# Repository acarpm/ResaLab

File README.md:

# ResaLab

---

**ResaLab** est un projet multidomaine ayant pour objectif de **simplifier et centraliser la procédure de réservation des ressources du FabLab**.  
Il vise à offrir une plateforme fiable, intuitive et interconnectée entre le site web, la base de données et les équipements physiques du FabLab.

---

# 📌 Module matériel – Interface HMI

Le module ResaLab est une **interface homme-machine (IHM)** destinée à être installée directement sur les équipements du FabLab :

- Imprimantes 3D  
- Brodeuses numériques  
- Découpeuses laser  

## 🧩 Composition du module

- 🖥️ Écran **e-ink 2.9"**
- 🔴🟠🟢 Trois LED haute puissance (3W)
- 🔘 Trois boutons lumineux
- 🧠 Module **ESP32-C3**
- ⚡ Alimentation USB-C
- 📐 PCB sur mesure (PCB-A)

---

# 🎯 Fonctionnalités principales

Le module permet :

- ✅ D’afficher l’état de la machine (Disponible / Réservée / En cours)
- 📅 De synchroniser les réservations avec le serveur
- 🔐 De valider localement la présence de l’utilisateur
- 💡 De fournir un retour visuel clair via LED haute puissance
- 🌐 De communiquer en Wi-Fi avec la plateforme centrale

---

# ⚙️ Configuration requise

Certaines constantes doivent être définies dans le firmware :

```cpp
const char* deviceId = "00000001";  // ID du device enregistré sur le serveur

Un fichier identifier.h doit être créé et contenir :

const char* ssid = "";
const char* password = "";
const String serverUrl = "";

``` 

Ce fichier doit être inclus dans le code principal.

---

## Architecture générale du projet

Le projet est divisé en plusieurs domaines complémentaires :

**Site Web**
Plateforme de réservation en ligne
Gestion des utilisateurs et des droits d'accès
Gestion des réservations (création, modification, consultation)
Base de données centralisée
Historique d’utilisation

**Gestion des transactions / crédits**
Carte électronique (ESP32-C3)
Interface Homme-Machine locale
Validation des réservations via API serveur
Autorisation d’accès à l’équipement

Affichage des informations sur écran e-ink
Pilotage des LED 3W
Communication Wi-Fi sécurisée

**Modélisation du boîtier**
Conception 3D du boîtier
Intégration ergonomique des boutons et LEDs
Adaptation aux contraintes d’impression 3D
Optimisation pour maintenance et production FabLab

Voici certaines contraintes à tenir en compte:
Alimentation
Entrée : 5V
Conversion vers 3.3V / 3A
Capacité 3A dimensionnée pour :

Pics Wi-Fi
LED haute puissance
Écran e-ink

## Gestion des LED 3W
Pads TP3 à TP8
Pilotage via transistors Q1, Q2, Q3
Couleurs :
🔴 Rouge
🟠 Orange
🟢 Vert

*GPIO LED*
green  = 0
orange = 9
red    = 1

*Boutons lumineux*
Pads TP9 à TP17

## Interface écran e-ink (SPI 4 lignes)

Écran 2.9 connecté via SPI. https://github.com/WeActStudio/WeActStudio.EpaperModule

Mapping GPIO
MOSI : 7
SCLK : 6
CS   : 10
DC   : 8
RST  : 3
BUSY : 2

Connexion prévue via dupont wires.

GPIO supplémentaires

Les GPIO restants sont exposés via le connecteur J3.
Permet d’ajouter des périphériques ou de réaliser des tests.

## État du projet

Version actuelle : PCB-A (Proof of Concept)

## État du projet

La première version de la PCB a servi de **Proof of Concept (PoC)**.

Une nouvelle révision est prévue afin de :

- Corriger les défauts de la V1
- Permettre la programmation directement via le port **USB-C d’alimentation**
- Simplifier l’intégration et améliorer la fiabilité

---

## Roadmap (prévisionnelle)

- [ ] Révision PCB V2
- [ ] Intégration module ESP32-C3
- [ ] Support complet OTA
- [ ] Intégration avec le système de réservation (backend ResaLab)

---

## Statut

Projet en développement actif.  
Version actuelle : Prototype fonctionnel (PoC).

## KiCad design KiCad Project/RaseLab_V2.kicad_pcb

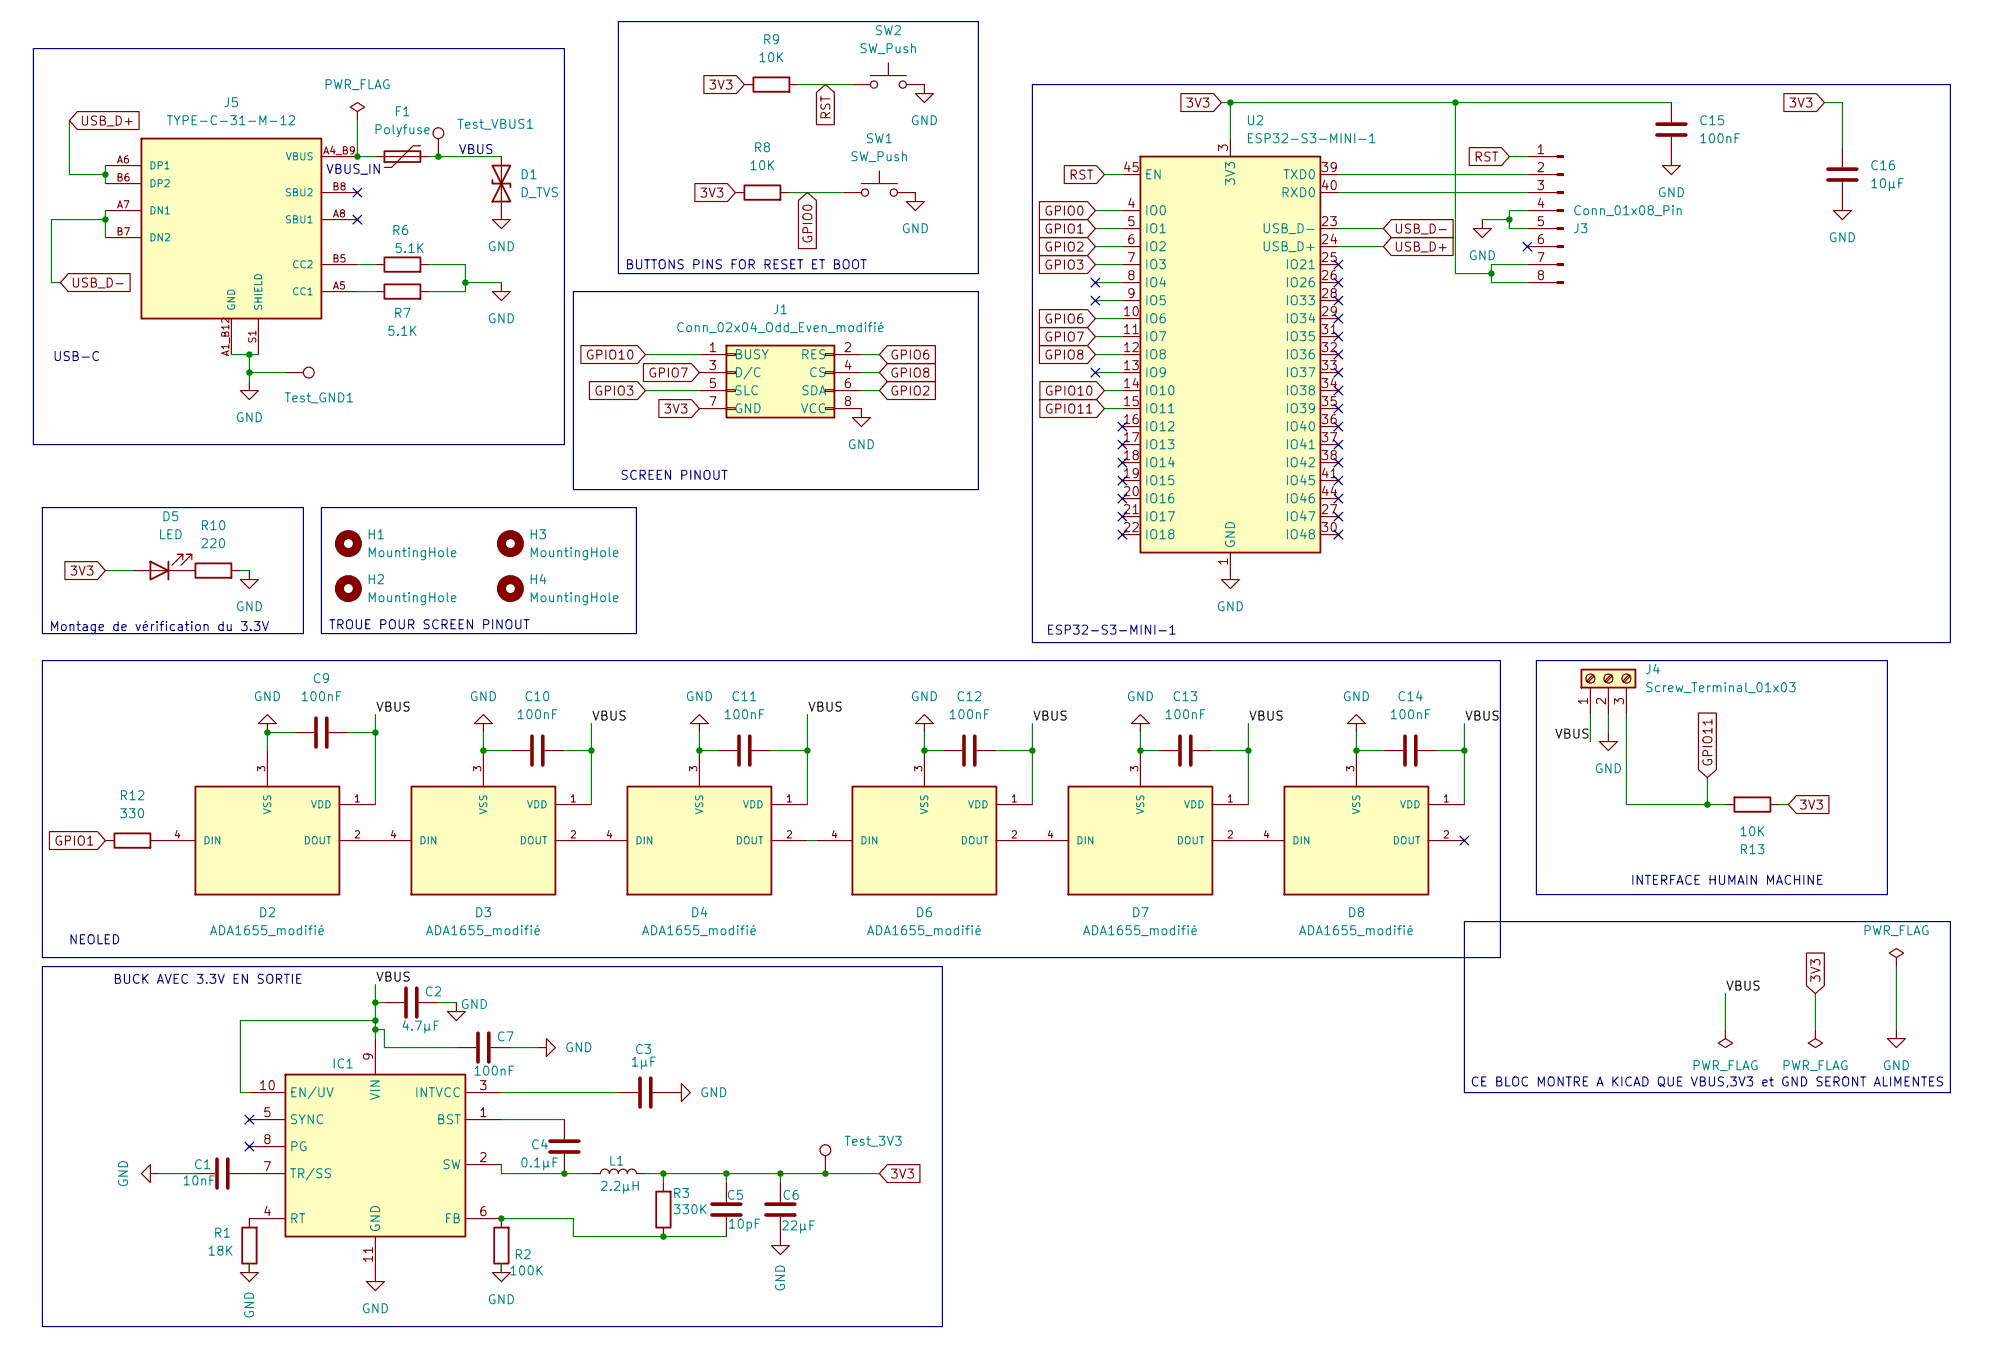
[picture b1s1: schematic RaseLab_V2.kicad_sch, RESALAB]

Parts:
C1: 10nF; C_0603_1608Metric
C2: 4.7µF; C_0603_1608Metric
C3: 1µF; C_0603_1608Metric
C4: 0.1µF; C_0603_1608Metric
C5: 10pF; C_0603_1608Metric
C6: 22µF; C_0603_1608Metric
C7, C9, C10, C11, C12, C13, C14, C15: 100nF; C_0603_1608Metric
C16: 10µF; C_0603_1608Metric
D1: D_TVS; D_SOD-123
D2, D3, D4, D6, D7, D8: ADA1655_modifié; LED_WS2812B_PLCC4_5.0x5.0mm_P3.2mm; PARTREV N/A
D5: LED; LED_0603_1608Metric
F1: Polyfuse; Fuse_1206_3216Metric
H1, H2, H3, H4: MountingHole; MountingHole_2.2mm_M2
IC1: LT8607EMSE#TRPBF; SOP50P490X110-11N; Mouser Part Number 584-LT8607EMSE#TRPBF
J1: Conn_02x04_Odd_Even_modifié; PinHeader_2x04_P2.54mm_Vertical
J3: Conn_01x08_Pin; PinHeader_1x08_P2.54mm_Horizontal
J4: Screw_Terminal_01x03; TerminalBlock_MaiXu_MX126-5.0-03P_1x03_P5.00mm
J5: TYPE-C-31-M-12; HRO_TYPE-C-31-M-12; PARTREV 2020.12.08
L1: 2.2µH; L_2010_5025Metric
R1: 18K; R_0603_1608Metric
R2: 100K; R_0603_1608Metric
R3: 330K; R_0603_1608Metric
R6, R7: 5.1K; R_0603_1608Metric
R8, R9, R13: 10K; R_0603_1608Metric
R10: 220; R_0603_1608Metric
R12: 330; R_0603_1608Metric
SW1, SW2: SW_Push; SW_SPST_PTS645Sx43SMTR92
Test_3V3: TestPoint; TestPoint_Pad_1.0x1.0mm
Test_GND1: TestPoint; TestPoint_Pad_1.0x1.0mm
Test_VBUS1: TestPoint; TestPoint_Pad_1.0x1.0mm
U2: ESP32-S3-MINI-1; XCVR_ESP32-S3-MINI-1-N8

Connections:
3V3: C5.2, C6.2, C15.1, C16.1, D5.2 (A), J1.7 (GND), J3.7, J3.8, L1.2, R3.2, R8.1, R9.1, R13.1, Test_3V3.1 (1_1), U2.3 (3V3)
GND: C1.2, C2.1, C3.1, C6.1, C7.1, C9.1, C10.1, C11.1, C12.1, C13.1, C14.1, C15.2, C16.2, D1.1 (A1), D2.3 (VSS), D3.3 (VSS), D4.3 (VSS), D6.3 (VSS), D7.3 (VSS), D8.3 (VSS), IC1.11 (GND), J1.8 (VCC), J3.4, J3.5, J4.2, J5.A1_B12 (GND), J5.S1 (SHIELD), R1.1, R2.1, R6.2, R7.2, R10.2, SW1.2, SW2.2, Test_GND1.1 (1_1), U2.1 (GND), U2.2 (GND), U2.42 (GND), U2.43 (GND), U2.46 (GND), U2.47 (GND), U2.48 (GND), U2.49 (GND), U2.50 (GND), U2.51 (GND), U2.52 (GND), U2.53 (GND), U2.54 (GND), U2.55 (GND), U2.56 (GND), U2.57 (GND), U2.58 (GND), U2.59 (GND), U2.60 (GND), U2.61 (GND), U2.62 (GND), U2.63 (GND), U2.64 (GND), U2.65 (GND)
GPIO0: R8.2, SW1.1, U2.4 (IO0)
GPIO1: R12.1, U2.5 (IO1)
GPIO2: J1.6 (SDA), U2.6 (IO2)
GPIO3: J1.5 (SLC), U2.7 (IO3)
GPIO6: J1.2 (RES), U2.10 (IO6)
GPIO7: J1.3 (D/C), U2.11 (IO7)
GPIO8: J1.4 (CS), U2.12 (IO8)
GPIO10: J1.1 (BUSY), U2.14 (IO10)
GPIO11: J4.3, R13.2, U2.15 (IO11)
unnamed: D1.2 (A2), F1.2, Test_VBUS1.1 (1_1)
unnamed: D2.4 (DIN), R12.2
unnamed: D2.2 (DOUT), D3.4 (DIN)
unnamed: D3.2 (DOUT), D4.4 (DIN)
unnamed: D4.2 (DOUT), D6.4 (DIN)
unnamed: D5.1 (K), R10.1
unnamed: D6.2 (DOUT), D7.4 (DIN)
unnamed: D7.2 (DOUT), D8.4 (DIN)
unnamed: C4.2, IC1.1 (BST)
unnamed: C5.1, IC1.6 (FB), R2.2, R3.1
unnamed: C3.2, IC1.3 (INTVCC)
unnamed: IC1.4 (RT), R1.2
unnamed: C4.1, IC1.2 (SW), L1.1
unnamed: C1.1, IC1.7 (TR/SS)
unnamed: J3.2, U2.39 (TXD0)
unnamed: J3.3, U2.40 (RXD0)
unnamed: J5.A5 (CC1), R7.1
unnamed: J5.B5 (CC2), R6.1
RST: J3.1, R9.2, SW2.1, U2.45 (EN)
USB_D+: J5.A6 (DP1), J5.B6 (DP2), U2.24 (USB_D+)
USB_D-: J5.A7 (DN1), J5.B7 (DN2), U2.23 (USB_D-)

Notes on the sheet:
USB-C
BUCK AVEC 3.3V EN SORTIE
VBUS_IN
TROUE POUR SCREEN PINOUT
SCREEN PINOUT
VBUS
INTERFACE HUMAIN MACHINE
CE BLOC MONTRE A KICAD QUE VBUS,3V3 et GND SERONT ALIMENTES
NEOLED
ESP32-S3-MINI-1
Montage de vérification du 3.3V
BUTTONS PINS FOR RESET ET BOOT

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
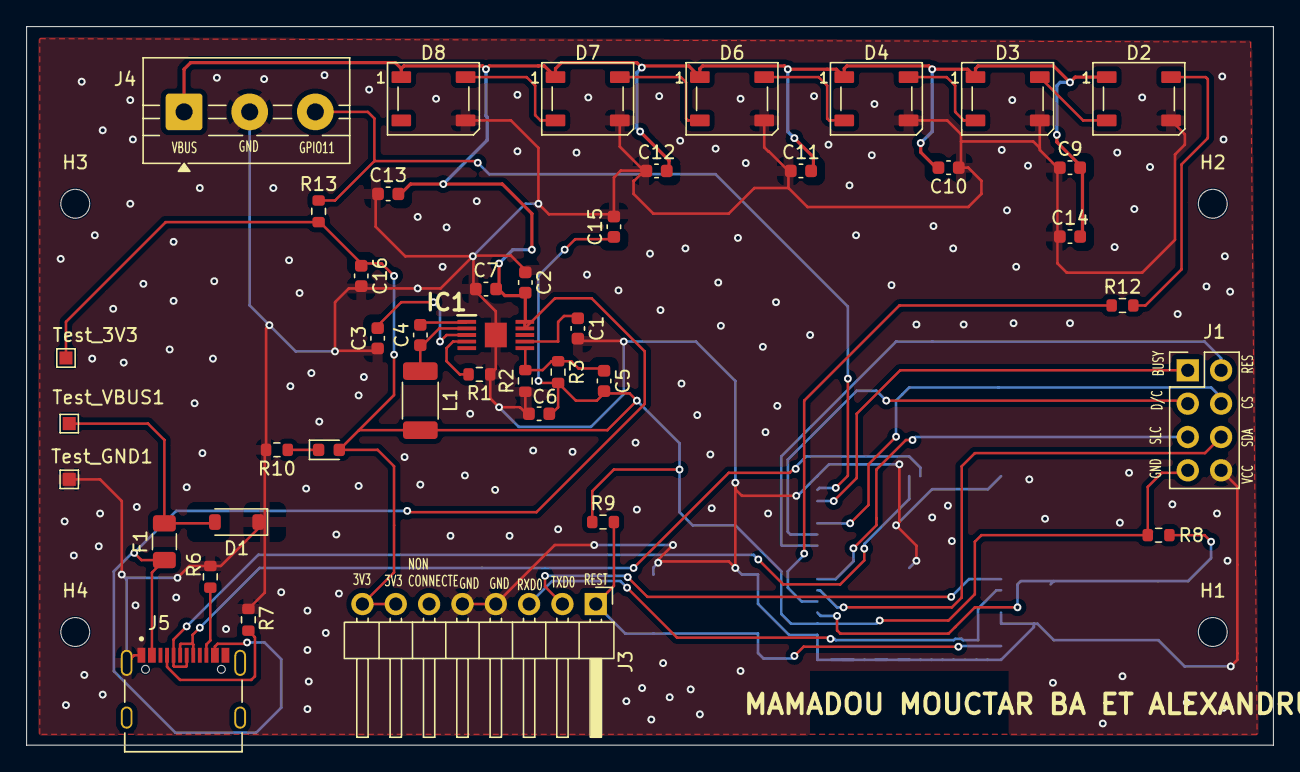
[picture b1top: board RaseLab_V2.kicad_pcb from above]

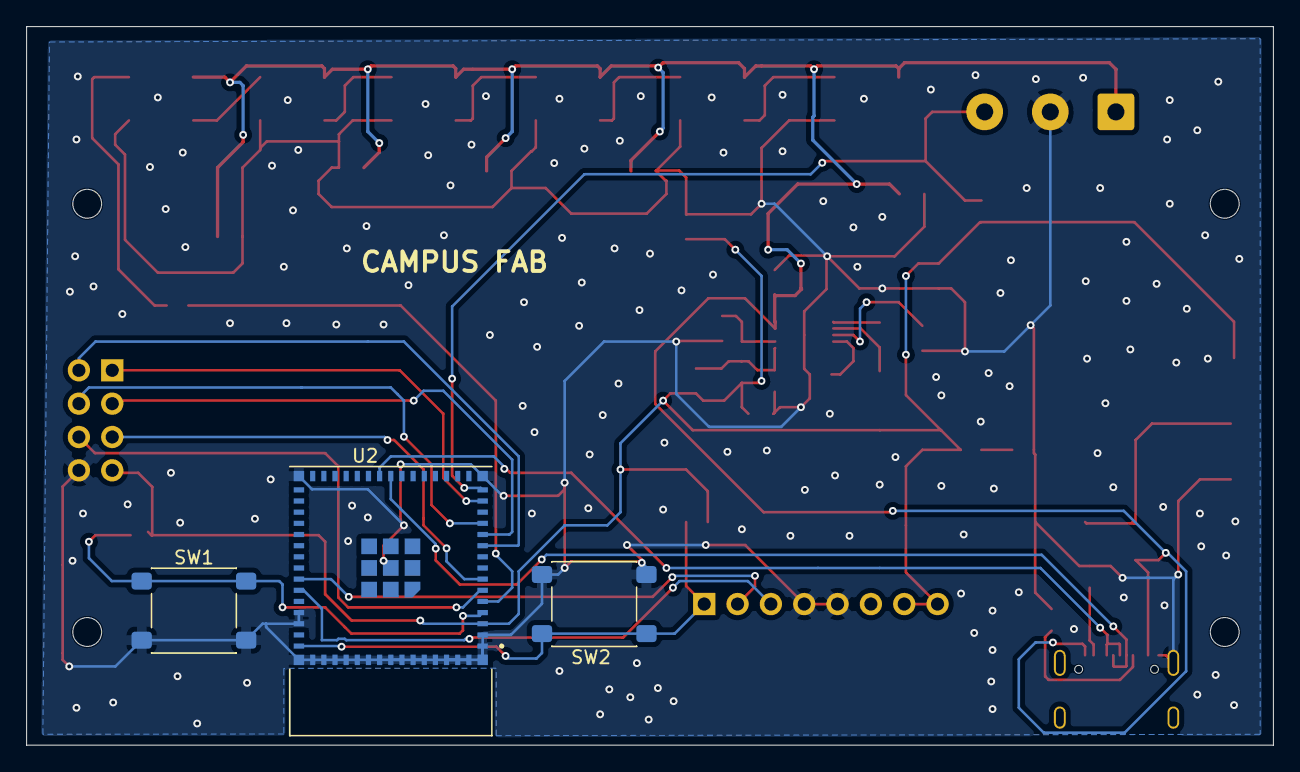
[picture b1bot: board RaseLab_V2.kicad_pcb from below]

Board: 2 copper layers, 95.0 x 54.8 mm, 50 parts (3 on the bottom side), 33 nets.

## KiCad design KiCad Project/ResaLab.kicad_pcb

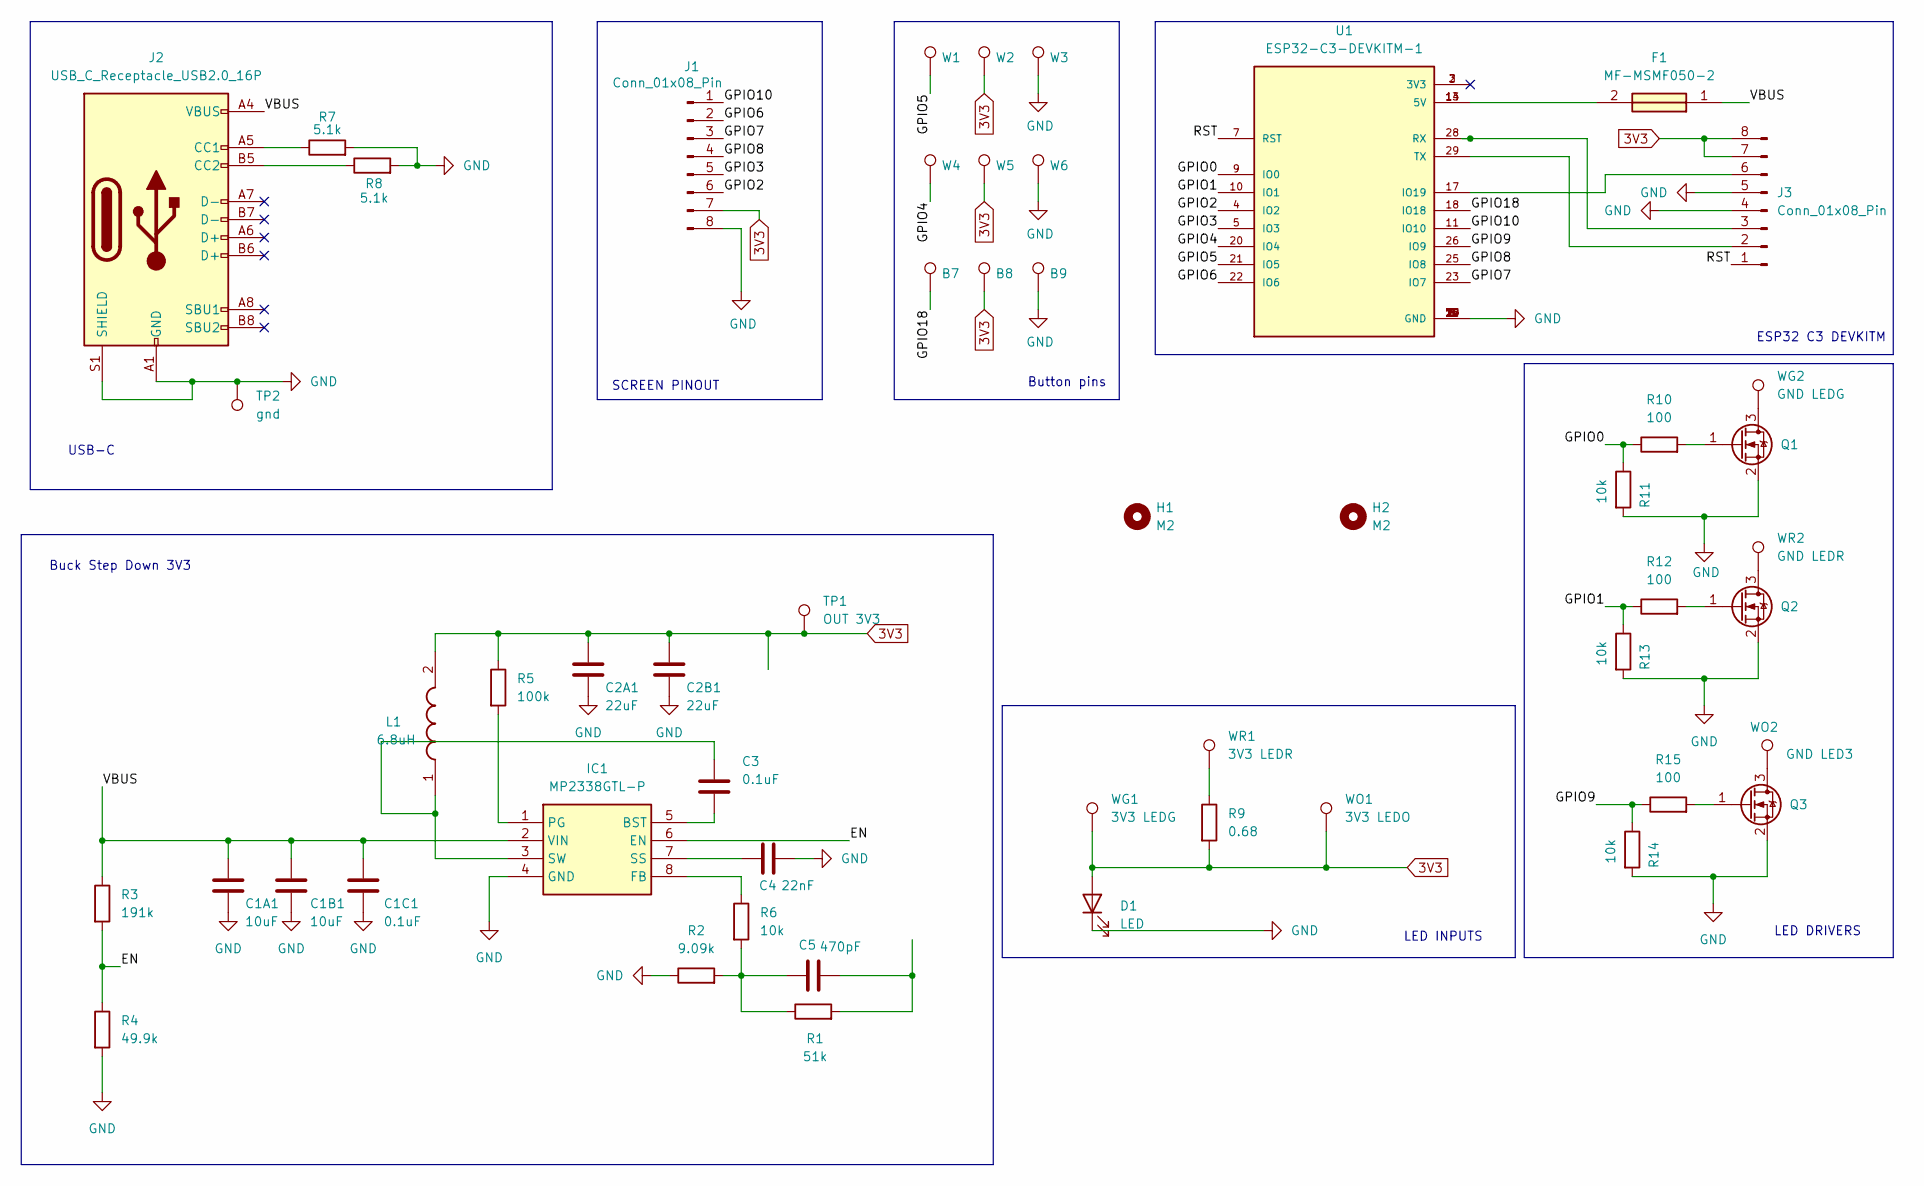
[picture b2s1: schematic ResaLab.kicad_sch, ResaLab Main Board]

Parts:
B7, B8, B9: SolderWirePad_1x01_SMD_1x2mm
C1A1, C1B1: 10uF; C_0805_2012Metric_Pad1.18x1.45mm_HandSolder
C1C1, C3: 0.1uF; C_0805_2012Metric_Pad1.18x1.45mm_HandSolder
C2A1, C2B1: 22uF; C_1206_3216Metric_Pad1.33x1.80mm_HandSolder
C4: 22nF; C_0805_2012Metric_Pad1.18x1.45mm_HandSolder
C5: 470pF; C_0805_2012Metric_Pad1.18x1.45mm_HandSolder
D1: LED; LED_0805_2012Metric_Pad1.15x1.40mm_HandSolder
F1: MF-MSMF050-2; FUSC4632X85N; Mouser Part Number 652-MF-MSMF050-2
H1, H2: M2; MountingHole_2.2mm_M2
IC1: MP2338GTL-P; SOTFL50P160X60-8N; Mouser Part Number 946-MP2338GTL-P
J1, J3: Conn_01x08_Pin; PinHeader_1x08_P2.54mm_Vertical
J2: USB_C_Receptacle_USB2.0_16P; USB_C_Receptacle_GCT_USB4105-xx-A_16P_TopMnt_Horizontal
L1: 6.8uH; MPLAL60606R8; Mouser Part Number 946-MPL-AL6060-6R8
Q1, Q2, Q3: AO3400A; SOT-23
R1: 51k; R_0805_2012Metric_Pad1.20x1.40mm_HandSolder
R2: 9.09k; R_0805_2012Metric_Pad1.20x1.40mm_HandSolder
R3: 191k; R_0805_2012Metric
R4: 49.9k; R_0805_2012Metric
R5: 100k; R_0805_2012Metric
R6, R11, R13, R14: 10k; R_0805_2012Metric_Pad1.20x1.40mm_HandSolder
R7, R8: 5.1k; R_0603_1608Metric_Pad0.98x0.95mm_HandSolder
R9: 0.68; R_2816_7142Metric_Pad3.20x4.45mm_HandSolder
R10, R12, R15: 100; R_0805_2012Metric_Pad1.20x1.40mm_HandSolder
TP1: OUT 3V3; TestPoint_Pad_D1.5mm
TP2: gnd; TestPoint_Pad_D1.5mm
U1: ESP32-C3-DEVKITM-1; XCVR_ESP32-C3-DEVKITM-1
W1, W2, W3, W4, W5, W6: SolderWirePad_1x01_SMD_1x2mm
WG1: 3V3 LEDG; SolderWirePad_1x01_SMD_1x2mm
WG2: GND LEDG; SolderWirePad_1x01_SMD_1x2mm
WO1: 3V3 LEDO; SolderWirePad_1x01_SMD_1x2mm
WO2: GND LED3; SolderWirePad_1x01_SMD_1x2mm
WR1: 3V3 LEDR; SolderWirePad_1x01_SMD_1x2mm
WR2: GND LEDR; SolderWirePad_1x01_SMD_1x2mm

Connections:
3V3: B8.1, C2A1.1, C2B1.1, D1.2 (A), J1.7, J3.7, J3.8, L1.2, R5.1, R9.2, TP1.1, W2.1, W5.1, WG1.1, WO1.1
/EN: IC1.6 (EN), R3.2, R4.1
/GPIO0: R10.1, R11.1, U1.9 (IO0)
/GPIO1: R12.1, R13.1, U1.10 (IO1)
/GPIO2: J1.6, U1.4 (IO2)
/GPIO3: J1.5, U1.5 (IO3)
/GPIO4: U1.20 (IO4), W4.1
/GPIO5: U1.21 (IO5), W1.1
/GPIO6: J1.2, U1.22 (IO6)
/GPIO7: J1.3, U1.23 (IO7)
/GPIO8: J1.4, U1.25 (IO8)
/GPIO9: R14.1, R15.1, U1.26 (IO9)
/GPIO10: J1.1, U1.11 (IO10)
/GPIO18: B7.1, U1.18 (IO18)
/RST: J3.1, U1.7 (RST)
/VBUS: C1A1.1, C1B1.1, C1C1.1, F1.1, IC1.2 (VIN), J2.A4 (VBUS), J2.A9 (VBUS), J2.B4 (VBUS), J2.B9 (VBUS), R3.1
GND: B9.1, C1A1.2, C1B1.2, C1C1.2, C2A1.2, C2B1.2, C4.2, D1.1 (K), IC1.4 (GND), J1.8, J2.A1 (GND), J2.A12 (GND), J2.B1 (GND), J2.B12 (GND), J2.S1 (SHIELD), J3.4, J3.5, Q1.2 (S), Q2.2 (S), Q3.2 (S), R2.1, R4.2, R7.2, R8.2, R11.2, R13.2, R14.2, TP2.1, U1.1 (GND), U1.6 (GND), U1.8 (GND), U1.12 (GND), U1.15 (GND), U1.16 (GND), U1.19 (GND), U1.24 (GND), U1.27 (GND), U1.30 (GND), W3.1, W6.1
unnamed: C5.1, R1.1, R2.2, R6.2
unnamed: C5.2, R1.2
unnamed: F1.2, U1.13 (5V), U1.14 (5V)
unnamed: C3.2, IC1.5 (BST)
unnamed: IC1.8 (FB), R6.1
unnamed: IC1.1 (PG), R5.2
unnamed: C4.1, IC1.7 (SS)
unnamed: C3.1, IC1.3 (SW), L1.1
unnamed: J2.A5 (CC1), R7.1
unnamed: J2.B5 (CC2), R8.1
unnamed: J3.2, U1.29 (TX)
unnamed: J3.3, U1.28 (RX)
unnamed: J3.6, U1.17 (IO19)
unnamed: Q1.3 (D), WG2.1
unnamed: Q1.1 (G), R10.2
unnamed: Q2.3 (D), WR2.1
unnamed: Q2.1 (G), R12.2
unnamed: Q3.3 (D), WO2.1
unnamed: Q3.1 (G), R15.2
unnamed: R9.1, WR1.1

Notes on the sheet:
ESP32 C3 DEVKITM
USB-C
LED DRIVERS
LED INPUTS
Buck Step Down 3V3
SCREEN PINOUT
Button pins

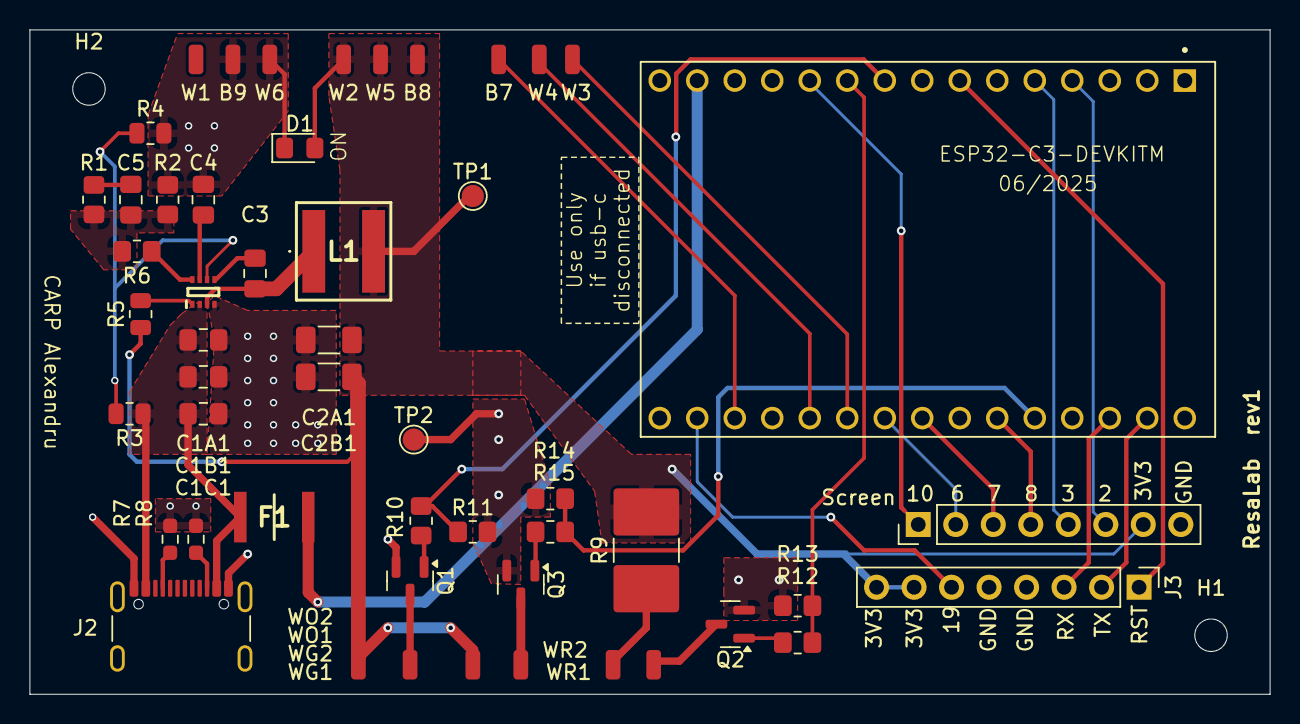
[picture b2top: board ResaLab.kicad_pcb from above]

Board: 2 copper layers, 84.0 x 45.0 mm, 53 parts (0 on the bottom side), 37 nets.

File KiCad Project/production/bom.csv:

Designator,Footprint,Quantity,Value,LCSC Part #
"B7, B8, B9, W1, W2, W3, W4, W5, W6",SolderWirePad_1x01_SMD_1x2mm,9,~,
"C1A1, C1B1",0805,2,10uF,
"C1C1, C3",0805,2,0.1uF,
"C2A1, C2B1",1206,2,22uF,
C4,0805,1,22nF,
C5,0805,1,470pF,
D1,0805,1,LED,
F1,FUSC4632X85N,1,MF-MSMF050-2,
IC1,SOTFL50P160X60-8N,1,MP2338GTL-P,
"J1, J3",PinHeader_1x08_P2.54mm_Vertical,2,Conn_01x08_Pin,
J2,USB_C_Receptacle_GCT_USB4105-xx-A_16P_TopMnt_Horizontal,1,USB_C_Receptacle_USB2.0_16P,
L1,MPLAL60606R8,1,6.8uH,
"Q1, Q2, Q3",SOT-23,3,AO3400A,
R1,0805,1,51k,
"R10, R12, R15",0805,3,100,
"R11, R13, R14, R6",0805,4,10k,
R2,0805,1,9.09k,
R3,0805,1,191k,
R4,0805,1,49.9k,
R5,0805,1,100k,
"R7, R8",0603,2,5.1k,
R9,2816,1,0.68,
TP1,TestPoint_Pad_D1.5mm,1,OUT 3V3,
TP2,TestPoint_Pad_D1.5mm,1,gnd,
U1,XCVR_ESP32-C3-DEVKITM-1,1,ESP32-C3-DEVKITM-1,
WG1,SolderWirePad_1x01_SMD_1x2mm,1,3V3 LEDG,
WG2,SolderWirePad_1x01_SMD_1x2mm,1,GND LEDG,
WO1,SolderWirePad_1x01_SMD_1x2mm,1,3V3 LEDO,
WO2,SolderWirePad_1x01_SMD_1x2mm,1,GND LED3,
WR1,SolderWirePad_1x01_SMD_1x2mm,1,3V3 LEDR,
WR2,SolderWirePad_1x01_SMD_1x2mm,1,GND LEDR,

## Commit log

2025-09-05 Loan 2.0
2025-09-05 AAAAAAAAAAAAAAAAAAAAAAAAA
    AAAAAAAAAAA
2025-09-09 New button and change State Reservation Request
2025-09-09 Resalab Working Without Screen
2025-09-09 Changing Reservation Time Delay
2025-10-31 Change RESERVATION_CANCELLED value from '2' to '4'
    Pfff compliqué la vie
2025-11-14 ScreenOutput
2025-11-21 Screen Display Loan
2025-11-24 Enhance README with project objectives and architecture
    Added detailed project objectives and architecture sections.
2025-11-24 Add technical constraints section to README
    Added technical constraints section detailing hardware specifications and functionalities.
2025-11-24 Update README with status badges and GPIO info removal
    Removed GPIO pin assignments and added status badges.
2025-11-24 Enhance README with project details
    Added project description and objectives to README.
2025-11-24 Showing name
2025-11-26 Progression Bar On Screen
2025-11-26 ScreenOutput Documentation
2025-11-27 ServerConnection.cpp Documentation
2025-11-27 Small changes
2025-11-27 Update README with configuration requirements
    Added required configuration details for firmware and identifier.h.
2025-11-27 Update deviceId in README to new value
2025-11-27 Small Small Changes
2025-11-28 CheckWifiConnection() fixed
2025-11-28 CheckConnection wifi changed
2026-03-02 Revise README for module details and project status; enhance configuration and functionality sections
2026-03-02 markdown fix
2026-03-02 Readme Fix
2026-03-02 Better Project Organisation
2026-06-05 Revert "Add files via upload"
    This reverts commit a9c3518be7772360b13313472f6971113314537d.
2026-06-05 feat(kicad): add name to component card
2026-06-08 RECTIFATION DE CERTAINS ERREURS
2026-06-08 AJOUT DES NONS SUR LES CONNECTEURS EXTERNES
